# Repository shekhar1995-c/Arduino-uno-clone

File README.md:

# Wifi-module-arduino

This project conists of the atmega 328p microntroller and can control the relay with the arduino

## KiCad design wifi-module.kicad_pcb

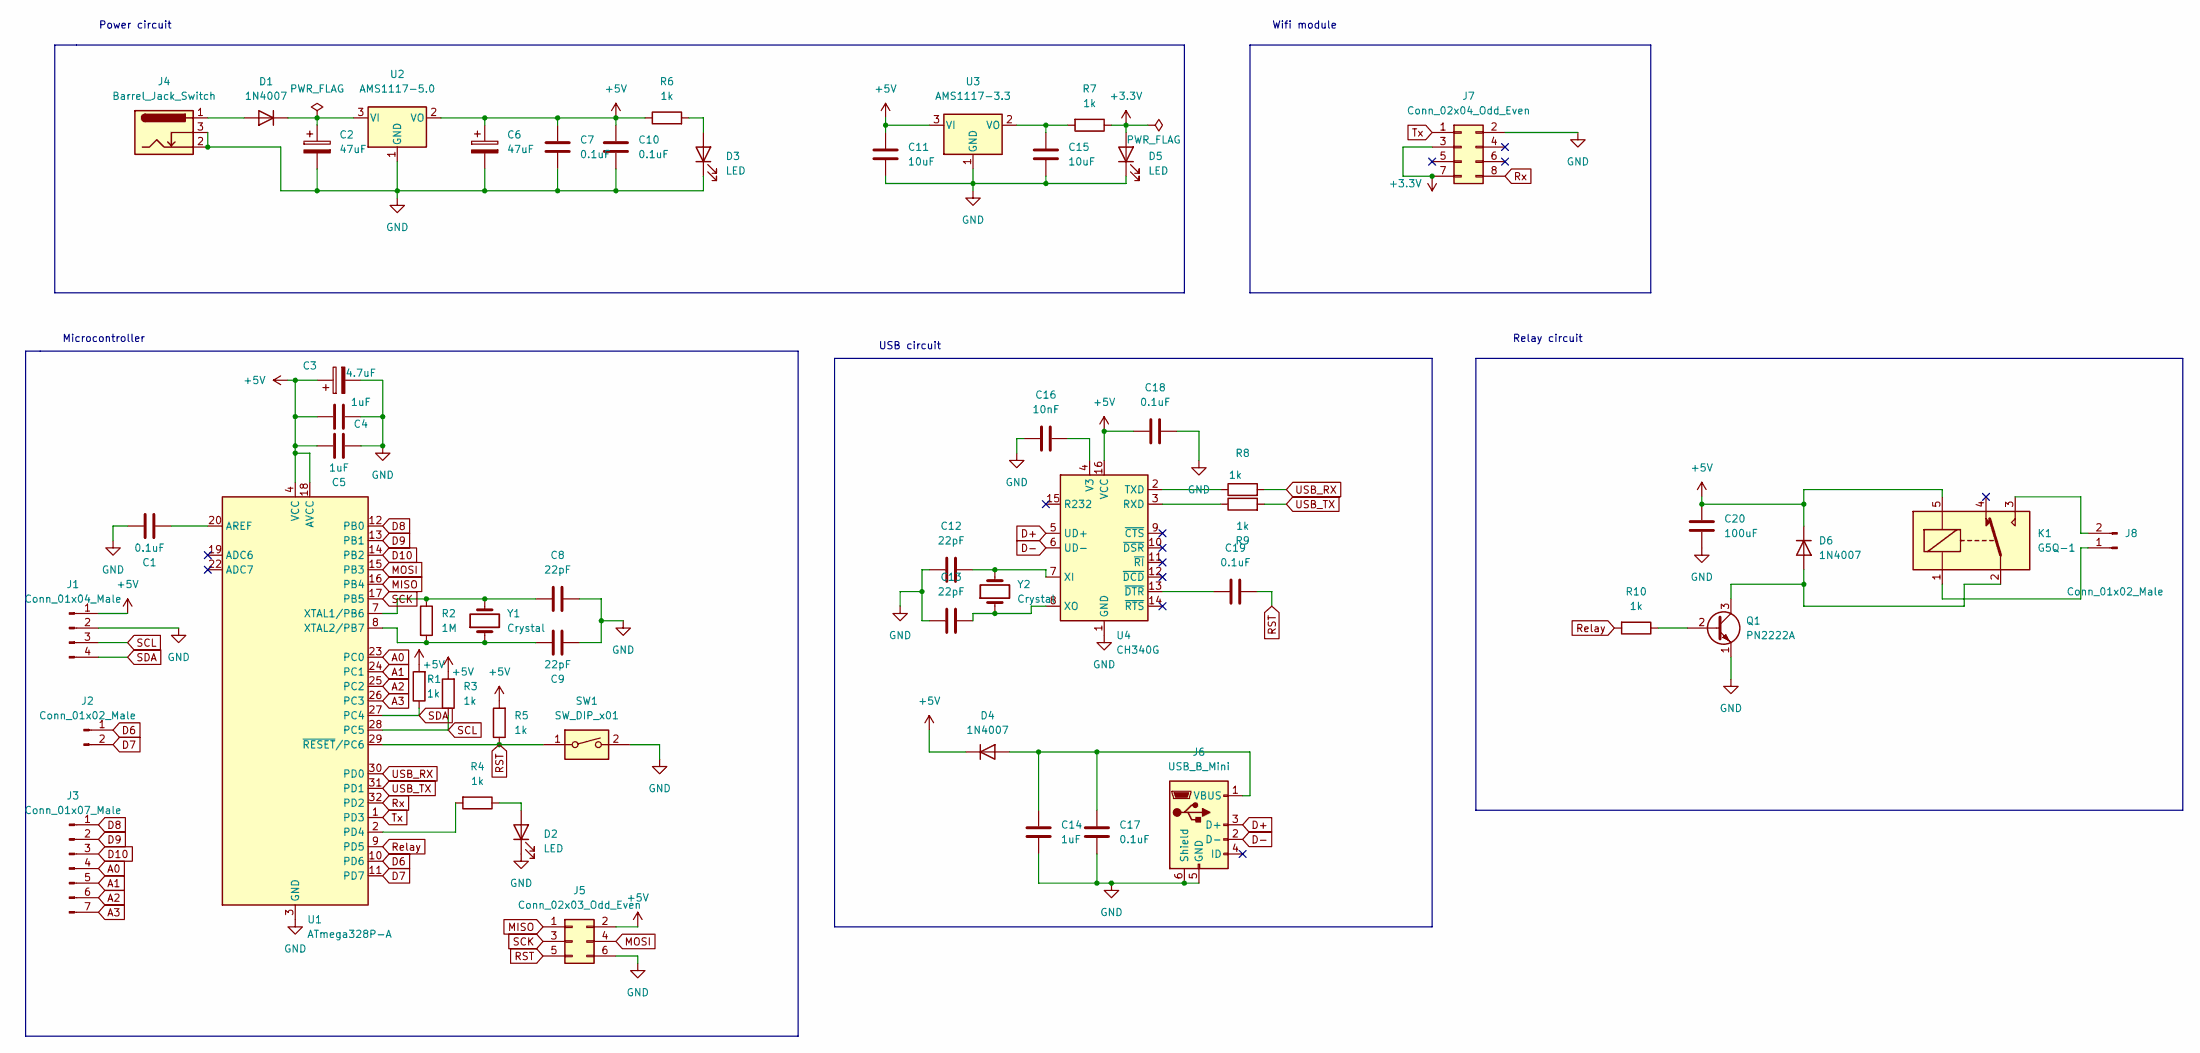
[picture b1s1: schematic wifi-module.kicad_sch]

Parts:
C1, C7, C10, C17, C18, C19: 0.1uF; C_0805_2012Metric
C2, C6: 47uF; CP_Elec_6.3x5.4
C3: 4.7uF; CP_Elec_6.3x5.4
C4, C5, C14: 1uF; C_0805_2012Metric
C8, C9, C12, C13: 22pF; C_0805_2012Metric
C11, C15: 10uF; C_0805_2012Metric
C16: 10nF; C_0805_2012Metric
C20: 100uF; C_0805_2012Metric
D1, D4, D6: 1N4007; D_SOD-123
D2, D3, D5: LED; LED_0603_1608Metric
J1: Conn_01x04_Male; PinHeader_1x04_P2.54mm_Vertical
J2: Conn_01x02_Male; PinHeader_1x02_P2.54mm_Vertical
J3: Conn_01x07_Male; PinHeader_1x07_P2.54mm_Vertical
J4: Barrel_Jack_Switch; BarrelJack_Horizontal
J5: Conn_02x03_Odd_Even; PinHeader_2x03_P2.54mm_Vertical
J6: USB_B_Mini; USB_Mini-B_Lumberg_2486_01_Horizontal
J7: Conn_02x04_Odd_Even; PinHeader_2x04_P2.54mm_Vertical
J8: Conn_01x02_Male; TerminalBlock_Phoenix_MKDS-1,5-2-5.08_1x02_P5.08mm_Horizont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
K1: G5Q-1; Relay_SPDT_SANYOU_SRD_Series_Form_C
Q1: PN2222A; TO-92_Inline
R1, R3, R4, R5, R6, R7, R8, R9, R10: 1k; R_0805_2012Metric
R2: 1M; R_0805_2012Metric
SW1: SW_DIP_x01; SW_PUSH_6mm
U1: ATmega328P-A; TQFP-32_7x7mm_P0.8mm
U2: AMS1117-5.0; SOT-223-3_TabPin2
U3: AMS1117-3.3; SOT-223-3_TabPin2
U4: CH340G; SOIC-16_3.9x9.9mm_P1.27mm
Y1, Y2: Crystal; Crystal_HC49-4H_Vertical

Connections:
+3V3: D5.2 (A), J7.3, J7.7, R7.1
+5V: C3.1, C4.1, C5.1, C6.1, C7.1, C10.1, C11.1, C18.1, C20.1, D4.1 (K), D6.1 (K), J1.1, J5.2, K1.5, R1.2, R3.2, R5.2, R6.1, U1.4 (VCC), U1.6 (VCC), U1.18 (AVCC), U2.2 (VO), U3.3 (VI), U4.16 (VCC)
A0: J3.4, U1.23 (PC0)
A1: J3.5, U1.24 (PC1)
A2: J3.6, U1.25 (PC2)
A3: J3.7, U1.26 (PC3)
D6: J2.1, U1.10 (PD6)
D7: J2.2, U1.11 (PD7)
D8: J3.1, U1.12 (PB0)
D9: J3.2, U1.13 (PB1)
D10: J3.3, U1.14 (PB2)
D+: J6.3 (D+), U4.5 (UD+)
D-: J6.2 (D-), U4.6 (UD-)
GND: C1.1, C2.2, C3.2, C4.2, C5.2, C6.2, C7.2, C8.2, C9.2, C10.2, C11.2, C12.1, C13.1, C14.1, C15.2, C16.1, C17.1, C18.2, C20.2, D2.1 (K), D3.1 (K), D5.1 (K), J1.2, J4.2, J4.3, J5.6, J6.5 (GND), J6.6 (Shield), J7.2, Q1.1 (E), SW1.2, U1.3 (GND), U1.5 (GND), U1.21 (GND), U2.1 (GND), U3.1 (GND), U4.1 (GND)
MISO: J5.1, U1.16 (PB4)
MOSI: J5.4, U1.15 (PB3)
unnamed: C1.2, U1.20 (AREF)
unnamed: C2.1, D1.1 (K), U2.3 (VI)
unnamed: C8.1, R2.1, U1.7 (XTAL1/PB6), Y1.2
unnamed: C9.1, R2.2, U1.8 (XTAL2/PB7), Y1.1
unnamed: C12.2, U4.7 (XI), Y2.2
unnamed: C13.2, U4.8 (XO), Y2.1
unnamed: C14.2, C17.2, D4.2 (A), J6.1 (VBUS)
unnamed: C15.1, R7.2, U3.2 (VO)
unnamed: C16.2, U4.4 (V3)
unnamed: C19.1, U4.13 (~DTR)
unnamed: D1.2 (A), J4.1
unnamed: D2.2 (A), R4.1
unnamed: D3.2 (A), R6.2
unnamed: D6.2 (A), K1.2, Q1.3 (C)
unnamed: J8.2, K1.3
unnamed: J8.1, K1.1
unnamed: Q1.2 (B), R10.1
unnamed: R4.2, U1.2 (PD4)
unnamed: R8.1, U4.2 (TXD)
unnamed: R9.1, U4.3 (RXD)
RST: C19.2, J5.5, R5.1, SW1.1, U1.29 (~RESET/PC6)
Relay: R10.2, U1.9 (PD5)
Rx: J7.8, U1.32 (PD2)
SCK: J5.3, U1.17 (PB5)
SCL: J1.3, R3.1, U1.28 (PC5)
SDA: J1.4, R1.1, U1.27 (PC4)
Tx: J7.1, U1.1 (PD3)
USB_RX: R8.2, U1.30 (PD0)
USB_TX: R9.2, U1.31 (PD1)

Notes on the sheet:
Power circuit
Wifi module
USB circuit
Relay circuit
Microcontroller

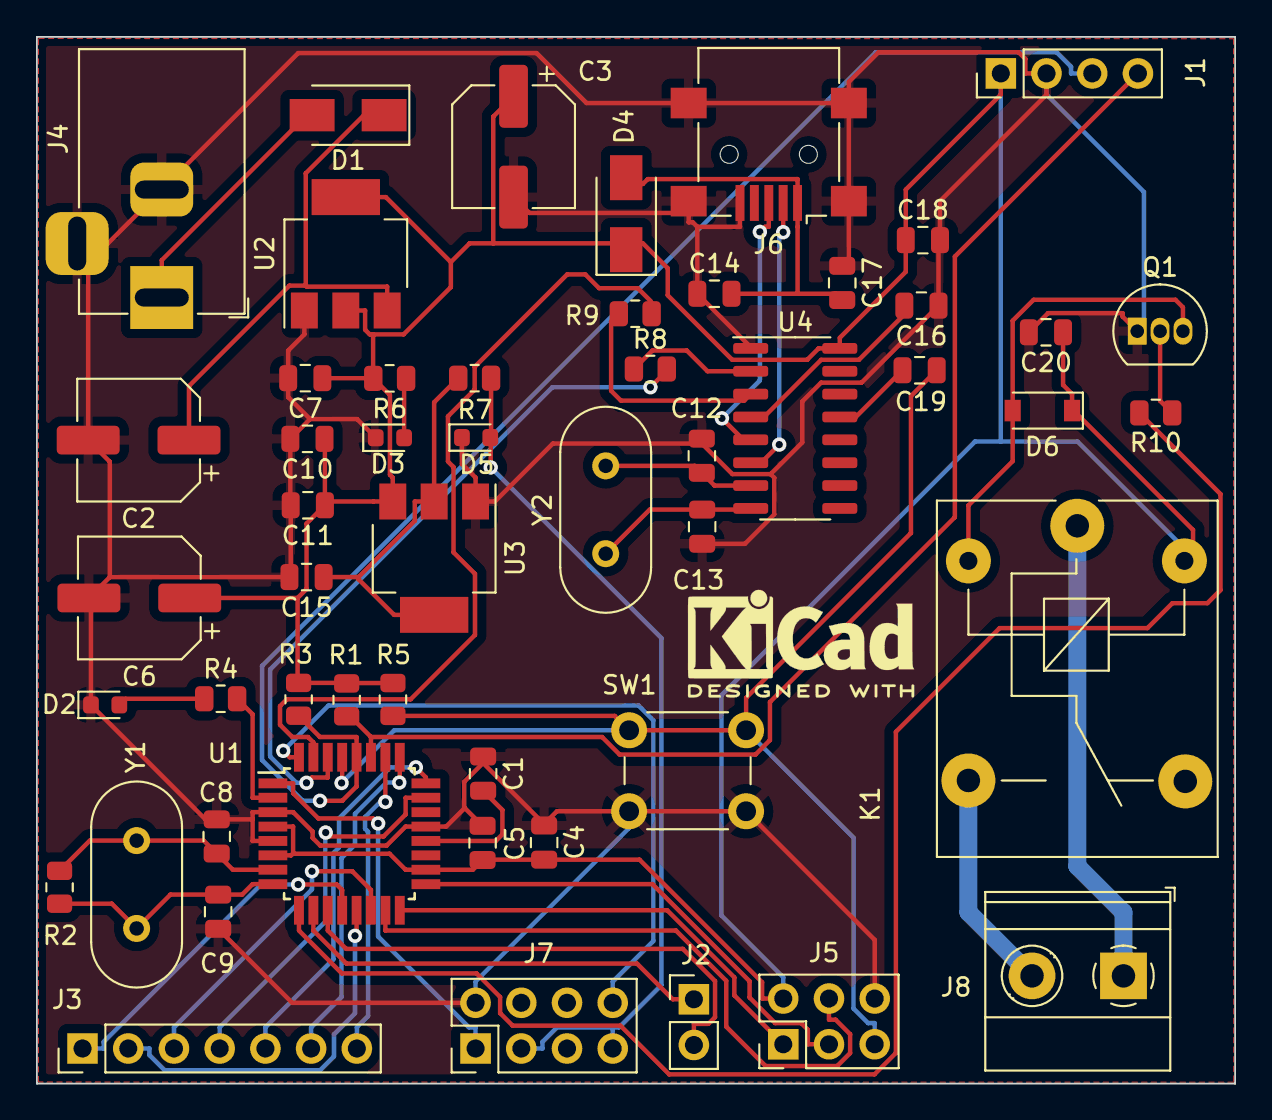
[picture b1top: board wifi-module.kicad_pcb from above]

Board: 2 copper layers, 66.6 x 58.2 mm, 53 parts (0 on the bottom side), 45 nets.

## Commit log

2022-10-30 new file added
2022-10-30 All files
2022-10-30 All Design files
